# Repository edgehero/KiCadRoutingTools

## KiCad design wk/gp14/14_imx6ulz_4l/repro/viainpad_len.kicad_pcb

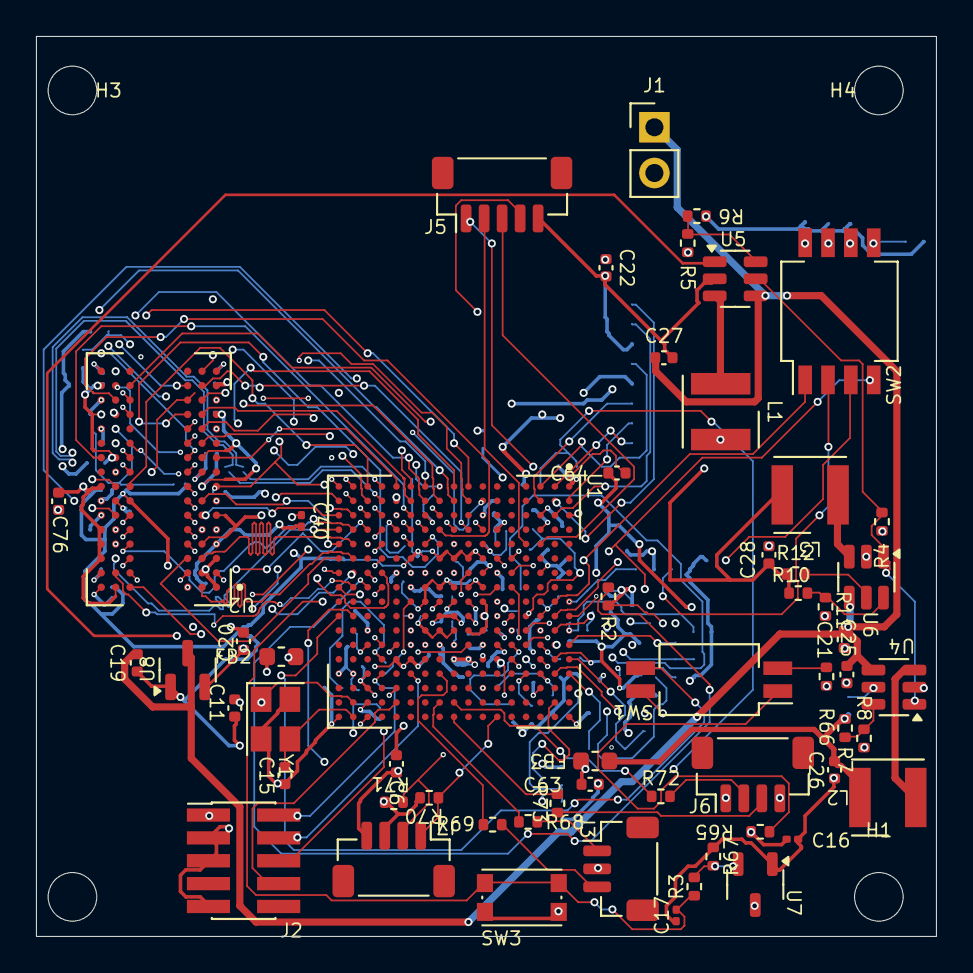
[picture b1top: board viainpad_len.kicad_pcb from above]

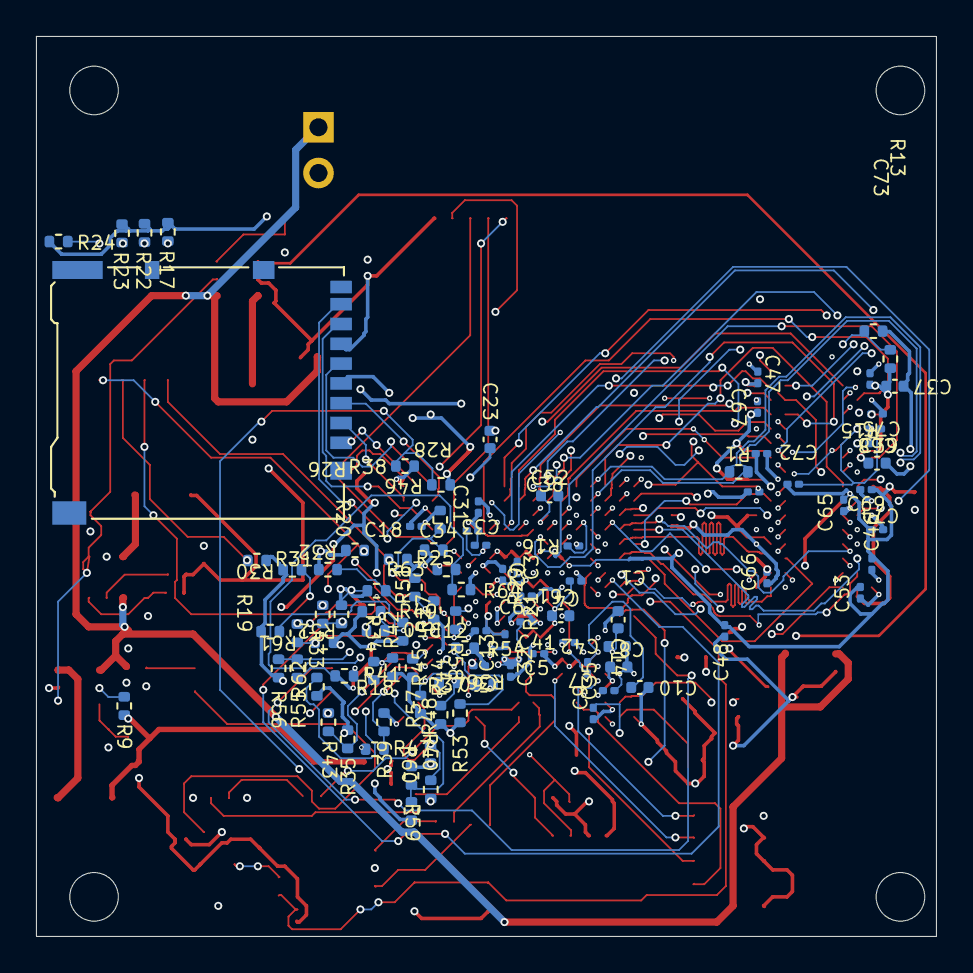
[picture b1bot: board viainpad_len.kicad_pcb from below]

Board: 4 copper layers, 50.0 x 50.0 mm, 159 parts (97 on the bottom side), 134 nets.

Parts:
C1, C2, C3, C5, C7, C9, C12, C13, C16, C17, C18, C31, C32, C33, C34, C35, C36, C38, C39, C40, C41, C46, C47, C48, C53, C60, C61, C62, C65, C66, C67, C69, C72, C73, C74, C75: 0.22u; C_0201_0603Metric
C4, C8, C23, C26, C28, C63, C68, C76: 22uF/20%/X5R/6.3V; C_0402_1005Metric
C6, C21, C25, C27, C37, C64: 4.7u; C_0402_1005Metric
C10, C42, C52: 10u; C_0402_1005Metric
C11, C15: 18p; C_0402_1005Metric
C14: 0.1u; C_0402_1005Metric
C19, C20: 1u; C_0402_1005Metric
C22: 10uF; C_0402_1005Metric
FB2, FB3: 120ohm@100MHz (2A); L_0603_1608Metric
H1, H2, H3, H4: MountingHole; MountingHole_2.7mm_M2.5
J1: Conn_01x02_Pin; PinHeader_1x02_P2.54mm_Vertical
J2: Conn_ARM_JTAG_SWD_10; PinHeader_2x05_P1.27mm_Vertical_SMD
J3: JST_BM03B-SRSS-TB; JST_SH_BM03B-SRSS-TB_1x03-1MP_P1.00mm_Vertical
J4: Micro_SD_Card_Det_Hirose_DM3AT; microSD_HC_Hirose_DM3AT-SF-PEJM5
J5: JST_BM05B-SRSS-TB; JST_SH_BM05B-SRSS-TB_1x05-1MP_P1.00mm_Vertical
J6, J7: JST_BM04B-SRSS-TB; JST_SH_BM04B-SRSS-TB_1x04-1MP_P1.00mm_Vertical
L1, L2, L3: 2.2uH; L_Wurth_WE-LQSH-4020
R1: 470R; R_0402_1005Metric
R2, R4, R9, R12, R25, R26, R27, R28, R29, R30, R31, R32, R33, R34, R35, R36, R37, R38, R39, R40, R41, R42, R43, R44, R45, R46, R47, R48, R49, R50, R51, R52, R53, R54, R55, R56, R57, R58, R59, R60, R61, R62, R63, R64, R65, R66: 10k; R_0402_1005Metric
R3, R17, R18, R19, R20, R21, R22, R23, R24: 1k; R_0402_1005Metric
R5, R8, R11, R67: 100k; R_0402_1005Metric
R6: 549k; R_0402_1005Metric
R7: 113k; R_0402_1005Metric
R10: 124k; R_0402_1005Metric
R13, R14, R71: 1.5k; R_0402_1005Metric
R15, R16: 240R; R_0201_0603Metric
R68, R69, R72, R73: 22R/R0402; R_0402_1005Metric
R70: 1.5K; R_0402_1005Metric
SW1: SW_DIP_x02; SW_DIP_SPSTx02_Slide_Copal_CHS-02B_W7.62mm_P1.27mm
SW2: SW_DIP_x04; SW_DIP_SPSTx04_Slide_Copal_CHS-04B_W7.62mm_P1.27mm
SW3: SW_Push; SW_Push_1P1T_NO_CK_KMR2
U1: MCIMX6Z0DVM09AB; BGA289C80P17X17_1400X1400X132
U2: K4B4G1646E-BCNB; BGA96C80P6X16_800X1400X120
U4, U5, U6: TLV62568DDC; SOT-23-6
U7: LM809; SOT-23-3
U8: MCP1700x-330xxTT; SOT-23
Y1: Crystal_GND24; Crystal_SMD_SeikoEpson_TSX3225-4Pin_3.2x2.5mm

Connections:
+1V2: C26.1, FB3.1, L2.2, R7.1, R9.1
+3V3: C16.1, C18.1, C22.1, C31.1, C32.1, C33.1, C34.1, C35.1, C60.1, FB2.1, J2.1 (VTref), J4.4 (VDD), J6.1, J7.3, L1.2, R2.2, R4.1, R6.1, R17.2, R18.2, R19.2, R20.2, R21.2, R22.2, R23.2, R24.2, R41.2, R42.2, R43.2, R44.2, R45.2, R46.2, R47.2, R48.2, R49.2, R51.2, R53.2, R55.2, R57.2, R59.2, R61.2, R63.2, R65.2, R66.2, R70.2, R71.2, U1.C4 (NVCC_SD1), U1.E7 (NVCC_NAND), U1.E13 (NVCC_GPIO3), U1.F4 (NVCC_SD2), U1.F13 (NVCC_KPP), U1.H13 (NVCC_UART), U1.J13 (NVCC_GPIO), U7.3 (VCC)
+5V: C19.1, C21.1, C25.1, C27.1, J1.1, U4.4 (VIN), U5.4 (VIN), U6.4 (VIN), U8.3 (VI)
/Boot Config, Clock, Reset/BOOT_CFG1_0: R25.2, SW2.1, U1.B9 (GPIO3_IO05)
/Boot Config, Clock, Reset/BOOT_CFG1_0_SW: R17.1, SW2.8
/Boot Config, Clock, Reset/BOOT_CFG1_1: R18.1, R26.2, U1.A9 (GPIO3_IO06)
/Boot Config, Clock, Reset/BOOT_CFG1_2: R19.1, R27.2, U1.E10 (GPIO3_IO07)
/Boot Config, Clock, Reset/BOOT_CFG1_3: R20.1, R28.2, U1.D10 (GPIO3_IO08)
/Boot Config, Clock, Reset/BOOT_CFG1_4: R21.1, R29.2, U1.C10 (GPIO3_IO09)
/Boot Config, Clock, Reset/BOOT_CFG1_5: R30.2, SW2.2, U1.B10 (GPIO3_IO10)
/Boot Config, Clock, Reset/BOOT_CFG1_5_SW: R22.1, SW2.7
/Boot Config, Clock, Reset/BOOT_CFG1_6: R31.2, SW2.3, U1.A10 (GPIO3_IO11)
/Boot Config, Clock, Reset/BOOT_CFG1_6_SW: R23.1, SW2.6
/Boot Config, Clock, Reset/BOOT_CFG1_7: R32.2, SW2.4, U1.D11 (GPIO3_IO12)
/Boot Config, Clock, Reset/BOOT_CFG1_7_SW: R24.1, SW2.5
/Boot Config, Clock, Reset/BOOT_CFG2_0: R49.1, R50.2, U1.B11 (GPIO3_IO13)
/Boot Config, Clock, Reset/BOOT_CFG2_1: R51.1, R52.2, U1.A11 (GPIO3_IO14)
/Boot Config, Clock, Reset/BOOT_CFG2_2: R53.1, R54.2, U1.E12 (GPIO3_IO15)
/Boot Config, Clock, Reset/BOOT_CFG2_3: R55.1, R56.2, U1.D12 (GPIO3_IO16)
/Boot Config, Clock, Reset/BOOT_CFG2_4: R57.1, R58.2, U1.C12 (GPIO3_IO17)
/Boot Config, Clock, Reset/BOOT_CFG2_5: R59.1, R60.2, U1.B12 (GPIO3_IO18)
/Boot Config, Clock, Reset/BOOT_CFG2_6: R61.1, R62.2, U1.A12 (GPIO3_IO19)
/Boot Config, Clock, Reset/BOOT_CFG2_7: R63.1, R64.2, U1.D13 (GPIO3_IO20)
/Boot Config, Clock, Reset/BOOT_CFG4_0: R33.2, R41.1, U1.C13 (GPIO3_IO21)
/Boot Config, Clock, Reset/BOOT_CFG4_1: R34.2, R42.1, U1.B13 (GPIO3_IO22)
/Boot Config, Clock, Reset/BOOT_CFG4_2: R35.2, R43.1, U1.A13 (GPIO3_IO23)
/Boot Config, Clock, Reset/BOOT_CFG4_3: R36.2, R44.1, U1.D14 (GPIO3_IO24)
/Boot Config, Clock, Reset/BOOT_CFG4_4: R37.2, R45.1, U1.C14 (GPIO3_IO25)
/Boot Config, Clock, Reset/BOOT_CFG4_5: R38.2, R46.1, U1.B14 (GPIO3_IO26)
/Boot Config, Clock, Reset/BOOT_CFG4_6: R39.2, R47.1, U1.A14 (GPIO3_IO27)
/Boot Config, Clock, Reset/BOOT_CFG4_7: R40.2, R48.1, U1.B16 (GPIO3_IO28)
/Boot Config, Clock, Reset/BOOT_MODE0: SW1.4, U1.T10 (BOOT_MODE0)
/Boot Config, Clock, Reset/BOOT_MODE1: SW1.3, U1.U10 (BOOT_MODE1)
/Boot Config, Clock, Reset/BOOT_MODE_PU_0: R65.1, SW1.1
/Boot Config, Clock, Reset/BOOT_MODE_PU_1: R66.1, SW1.2
/Boot Config, Clock, Reset/I2C2_SCL: J7.1, R70.1, U1.F17 (I2C2_SCL)
/Boot Config, Clock, Reset/I2C2_SDA: J7.2, R71.1, U1.G13 (I2C2_SDA)
/Boot Config, Clock, Reset/IMX_XI: C11.1, U1.T16 (XTALI), Y1.1
/Boot Config, Clock, Reset/IMX_XO: C15.1, U1.T17 (XTALO), Y1.3
/Boot Config, Clock, Reset/JTAG_TCK: J2.4 (SWDCLK/TCK), U1.M14 (JTAG_TCK)
/Boot Config, Clock, Reset/JTAG_TDI: J2.8 (NC/TDI), U1.N16 (JTAG_TDI)
/Boot Config, Clock, Reset/JTAG_TDO: J2.6 (SWO/TDO), U1.N15 (JTAG_TDO)
/Boot Config, Clock, Reset/JTAG_TMS: J2.2 (SWDIO/TMS), U1.P14 (JTAG_TMS)
/Boot Config, Clock, Reset/NVCC_PLL_OUT: C9.1, C10.1, U1.P13 (NVCC_PLL)
/Boot Config, Clock, Reset/RST_DLY_L: R3.2, R67.1, U7.2 (~RESET)
/Boot Config, Clock, Reset/SOC_ONOFF: R2.1, U1.R8 (ONOFF)
/Boot Config, Clock, Reset/SOC_RST_L: C17.2, R3.1, SW3.1, U1.P8 (POR_B)
/DRAM/DDRCTL_ZQ: R16.1, U1.N4 (DRAM_ZQPAD)
/DRAM/DRAM_AD0: U1.L5 (DRAM_ADDR00), U2.N3 (A0)
/DRAM/DRAM_AD1: U1.H2 (DRAM_ADDR01), U2.P7 (A1)
/DRAM/DRAM_AD2: U1.K1 (DRAM_ADDR02), U2.P3 (A2)
/DRAM/DRAM_AD3: U1.M2 (DRAM_ADDR03), U2.N2 (A3)
/DRAM/DRAM_AD4: U1.K4 (DRAM_ADDR04), U2.P8 (A4)
/DRAM/DRAM_AD5: U1.L1 (DRAM_ADDR05), U2.P2 (A5)
/DRAM/DRAM_AD6: U1.G2 (DRAM_ADDR06), U2.R8 (A6)
/DRAM/DRAM_AD7: U1.H4 (DRAM_ADDR07), U2.R2 (A7)
/DRAM/DRAM_AD8: U1.J4 (DRAM_ADDR08), U2.T8 (A8)
/DRAM/DRAM_AD9: U1.L2 (DRAM_ADDR09), U2.R3 (A9)
/DRAM/DRAM_AD10: U1.M4 (DRAM_ADDR10), U2.L7 (A10/AP)
/DRAM/DRAM_AD11: U1.K3 (DRAM_ADDR11), U2.R7 (A11)
/DRAM/DRAM_AD12: U1.L4 (DRAM_ADDR12), U2.N7 (A12/~BC)
/DRAM/DRAM_BA0: U1.M1 (DRAM_SDBA0), U2.M2 (BA0)
/DRAM/DRAM_BA1: U1.H1 (DRAM_SDBA1), U2.N8 (BA1)
/DRAM/DRAM_BA2: U1.K2 (DRAM_SDBA2), U2.M3 (BA2)
/DRAM/DRAM_CAS_L: U1.J2 (DRAM_CAS_B), U2.K3 (~CAS)
/DRAM/DRAM_CKE: U1.M3 (DRAM_SDCKE0), U2.K9 (CKE)
/DRAM/DRAM_CLK0_N: R1.2, U1.P2 (DRAM_SDCLK0_N), U2.K7 (~CK)
/DRAM/DRAM_CLK0_P: R1.1, U1.P1 (DRAM_SDCLK0_P), U2.J7 (CK)
/DRAM/DRAM_CS0_L: U1.N2 (DRAM_CS0_B), U2.L2 (~CS)
/DRAM/DRAM_DQ0: U1.T4 (DRAM_DATA00), U2.D7 (DQ8)
/DRAM/DRAM_DQ1: U1.U6 (DRAM_DATA01), U2.C3 (DQ9)
/DRAM/DRAM_DQ2: U1.T6 (DRAM_DATA02), U2.A2 (DQ13)
/DRAM/DRAM_DQ3: U1.U7 (DRAM_DATA03), U2.A3 (DQ15)
/DRAM/DRAM_DQ4: U1.U8 (DRAM_DATA04), U2.A7 (DQ12)
/DRAM/DRAM_DQ5: U1.T8 (DRAM_DATA05), U2.B8 (DQ14)
/DRAM/DRAM_DQ6: U1.T5 (DRAM_DATA06), U2.C2 (DQ11)
/DRAM/DRAM_DQ7: U1.U4 (DRAM_DATA07), U2.C8 (DQ10)
/DRAM/DRAM_DQ8: U1.U2 (DRAM_DATA08), U2.E3 (DQ0)
/DRAM/DRAM_DQ9: U1.U3 (DRAM_DATA09), U2.F2 (DQ2)
/DRAM/DRAM_DQ10: U1.U5 (DRAM_DATA10), U2.G2 (DQ6)
/DRAM/DRAM_DQ11: U1.R4 (DRAM_DATA11), U2.F8 (DQ3)
/DRAM/DRAM_DQ12: U1.P5 (DRAM_DATA12), U2.F7 (DQ1)
/DRAM/DRAM_DQ13: U1.P3 (DRAM_DATA13), U2.H3 (DQ4)
/DRAM/DRAM_DQ14: U1.R2 (DRAM_DATA14), U2.H8 (DQ5)
/DRAM/DRAM_DQ15: U1.R1 (DRAM_DATA15), U2.H7 (DQ7)
/DRAM/DRAM_DQM0: U1.T7 (DRAM_DQM0), U2.D3 (UDM)
/DRAM/DRAM_DQM1: U1.T3 (DRAM_DQM1), U2.E7 (LDM)
/DRAM/DRAM_DQS0_N: U1.P7 (DRAM_SDQS0_N), U2.B7 (~UDQS)
/DRAM/DRAM_DQS0_P: U1.P6 (DRAM_SDQS0_P), U2.C7 (UDQS)
/DRAM/DRAM_DQS1_N: U1.T2 (DRAM_SDQS1_N), U2.G3 (~LDQS)
/DRAM/DRAM_DQS1_P: U1.T1 (DRAM_SDQS1_P), U2.F3 (LDQS)
/DRAM/DRAM_ODT: U1.N1 (DRAM_ODT0), U2.K1 (ODT)
/DRAM/DRAM_RAS_L: U1.M5 (DRAM_RAS_B), U2.J3 (~RAS)
/DRAM/DRAM_RST_L: U1.G4 (DRAM_RESET), U2.T2 (~RESET)
/DRAM/DRAM_VREF: C36.2, C38.1, C39.1, C40.1, R13.2, R14.1, U1.P4 (DRAM_VREF), U2.H1 (VREFDQ), U2.M8 (VREFCA)
/DRAM/DRAM_WE_L: U1.J1 (DRAM_SDWE_B), U2.L3 (~WE)
/DRAM/DRAM_ZQ: R15.1, U2.L8 (ZQ)
/IO and Peripherals/FTDI_RXD: J3.1, R68.2
/IO and Peripherals/FTDI_TXD: J3.3, R69.2
/IO and Peripherals/QSPIA_CS_L: J5.4, U1.E6 (NAND_DQS)
/IO and Peripherals/QSPIA_D0: J5.1, U1.A3 (NAND_READY_B)
/IO and Peripherals/QSPIA_D1: J5.3, U1.C5 (NAND_CE0_B)
/IO and Peripherals/QSPIA_SCLK: J5.2, U1.D5 (NAND_WP_B)
/IO and Peripherals/UART1_RX: R68.1, U1.K16 (UART1_RX_DATA)
/IO and Peripherals/UART1_TX: R69.1, U1.K14 (UART1_TX_DATA)
/IO and Peripherals/UART2_RX: R72.1, U1.J16 (UART2_RX_DATA)
/IO and Peripherals/UART2_RX_R: J6.2, R72.2
/IO and Peripherals/UART2_TX: R73.1, U1.J17 (UART2_TX_DATA)
/IO and Peripherals/UART2_TX_R: J6.3, R73.2
/SDcard/SD1_CLK: J4.5 (CLK), U1.C1 (SD1_CLK)
/SDcard/SD1_CMD: J4.3 (CMD), U1.C2 (SD1_CMD)
/SDcard/SD1_D0: J4.7 (DAT0), U1.B3 (SD1_DATA0)
/SDcard/SD1_D1: J4.8 (DAT1), U1.B2 (SD1_DATA1)
/SDcard/SD1_D2: J4.1 (DAT2), U1.B1 (SD1_DATA2)
/SDcard/SD1_D3: J4.2 (DAT3/CD), U1.A2 (SD1_DATA3)
/SOC Power/V1P27_FB: R7.2, R8.1, U4.6 (FB)
/SOC Power/V1P27_PG: R9.2, U4.5 (PG)
/SOC Power/V1P27_SW: L2.1, U4.3 (SW)
/SOC Power/V3P3_FB: R5.1, R6.2, U5.6 (FB)
/SOC Power/V3P3_PG: R4.2, U4.1 (EN), U5.5 (PG), U6.1 (EN)
/SOC Power/V3P3_SW: L1.1, U5.3 (SW)
/SOC Power/VDD_ARM_CAP: C12.1, C13.1, C23.1, U1.G9 (VDD_ARM_CAP), U1.G10 (VDD_ARM_CAP__1), U1.G11 (VDD_ARM_CAP__2), U1.H11 (VDD_ARM_CAP__3)
/SOC Power/VDD_ARM_SOC_IN: C61.1, C62.1, C63.1, C64.1, FB3.2, U1.H9 (VDD_SOC_IN), U1.H10 (VDD_SOC_IN__1), U1.J9 (VDD_SOC_IN__2), U1.J10 (VDD_SOC_IN__3), U1.K9 (VDD_SOC_IN__4), U1.K10 (VDD_SOC_IN__5)
/SOC Power/VDD_HIGH_CAP: C7.1, C8.1, U1.R14 (VDD_HIGH_CAP), U1.R15 (VDD_HIGH_CAP__1)
/SOC Power/VDD_HIGH_IN: C5.1, C6.1, FB2.2, U1.L13 (VDD_HIGH_IN), U1.M13 (VDD_HIGH_IN__1), U1.N13 (VDD_HIGH_IN__2)
/SOC Power/VDD_SNVS_CAP: C41.1, U1.N12 (VDD_SNVS_CAP)
/SOC Power/VDD_SNVS_IN: C20.1, U1.P12 (VDD_SNVS_IN), U5.1 (EN), U8.2 (VO)
/SOC Power/VDD_SOC_CAP: C1.1, C2.1, C3.1, C4.1, U1.G8 (VDD_SOC_CAP), U1.H8 (VDD_SOC_CAP__1), U1.J8 (VDD_SOC_CAP__2), U1.J11 (VDD_SOC_CAP__3), U1.K8 (VDD_SOC_CAP__4), U1.K11 (VDD_SOC_CAP__5), U1.L8 (VDD_SOC_CAP__6), U1.L9 (VDD_SOC_CAP__7), U1.L10 (VDD_SOC_CAP__8), U1.L11 (VDD_SOC_CAP__9)
/SOC Power/VDD_USB_CAP: C14.1, C42.1, U1.R12 (VDD_USB_CAP)
/SOC Power/VMEM_FB: R10.2, R11.1, U6.6 (FB)
/SOC Power/VMEM_PG: R12.2, U6.5 (PG)
/SOC Power/VMEM_SW: L3.1, U6.3 (SW)
GND: C1.2, C2.2, C3.2, C4.2, C5.2, C6.2, C7.2, C8.2, C9.2, C10.2, C11.2, C12.2, C13.2, C14.2, C15.2, C16.2, C17.1, C18.2, C19.2, C20.2, C21.2, C22.2, C23.2, C25.2, C26.2, C27.2, C28.2, C31.2, C32.2, C33.2, C34.2, C35.2, C37.2, C38.2, C39.2, C40.2, C41.2, C42.2, C46.2, C47.2, C48.2, C52.2, C53.2, C60.2, C61.2, C62.2, C63.2, C64.2, C65.2, C66.2, C67.2, C68.2, C69.2, C72.2, C73.2, C74.2, C75.2, C76.2, J1.2, J2.3 (GND), J2.5 (GND), J2.9 (GNDDetect), J3.2, J4.6 (VSS), J5.5, J6.4, J7.4, R5.2, R8.2, R11.2, R14.2, R15.2, R16.2, R25.1, R26.1, R27.1, R28.1, R29.1, R30.1, R31.1, R32.1, R33.1, R34.1, R35.1, R36.1, R37.1, R38.1, R39.1, R40.1, R50.1, R52.1, R54.1, R56.1, R58.1, R60.1, R62.1, R64.1, R67.2, SW3.2, U1.A1 (VSS), U1.A17 (VSS__1), U1.C3 (VSS__2), U1.C7 (VSS__3), U1.C11 (VSS__4), U1.C15 (VSS__5), U1.E8 (VSS__6), U1.E11 (VSS__7), U1.F6 (VSS__8), U1.F7 (VSS__9), U1.F8 (VSS_1), U1.F9 (VSS_1__1), U1.F10 (VSS_1__2), U1.F11 (VSS_1__3), U1.F12 (VSS_1__4), U1.G3 (VSS_1__5), U1.G5 (VSS_1__6), U1.G7 (VSS_1__7), U1.G12 (VSS_1__8), U1.G15 (VSS_1__9), U1.H7 (VSS_2), U1.H12 (VSS_2__1), U1.J5 (VSS_2__2), U1.J7 (VSS_2__3), U1.J12 (VSS_2__4), U1.K7 (VSS_2__5), U1.K12 (VSS_2__6), U1.L3 (VSS_2__7), U1.L7 (VSS_2__8), U1.L12 (VSS_2__9), U1.M7 (VSS_3), U1.M8 (VSS_3__1), U1.M9 (VSS_3__2), U1.M10 (VSS_3__3), U1.M11 (VSS_3__4), U1.M12 (NGND_KEL0), U1.N3 (VSS_3__5), U1.N5 (VSS_3__6), U1.N7 (TEST_MODE), U1.R3 (VSS_3__7), U1.R5 (VSS_3__8), U1.R7 (VSS_3__9), U1.R11 (VSS_4), U1.R16 (VSS_4__1), U1.R17 (VSS_4__2), U1.T14 (VSS_4__3), U1.U1 (VSS_4__4), U1.U14 (VSS_4__5), U1.U17 (VSS_4__6), U2.A9 (VSS), U2.B1 (VSSQ), U2.B3 (VSS__1), U2.B9 (VSSQ__1), U2.D1 (VSSQ__2), U2.D8 (VSSQ__3), U2.E1 (VSS__2), U2.E2 (VSSQ__4), U2.E8 (VSSQ__5), U2.F9 (VSSQ__6), U2.G1 (VSSQ__7), U2.G8 (VSS__3), U2.G9 (VSSQ__8), U2.J2 (VSS__4), U2.J8 (VSS__5), U2.M1 (VSS__6), U2.M9 (VSS__7), U2.P1 (VSS__8), U2.P9 (VSS__9), U2.T1 (VSS__10), U2.T9 (VSS__11), U4.2 (GND), U5.2 (GND), U6.2 (GND), U7.1 (GND), U8.1 (GND), Y1.2, Y1.4
VMEM: C28.1, C36.1, C37.1, C46.1, C47.1, C48.1, C52.1, C53.1, C65.1, C66.1, C67.1, C68.1, C69.1, C72.1, C73.1, C74.1, C75.1, C76.1, L3.2, R10.1, R12.1, R13.1, U1.G6 (NVCC_DRAM), U1.H6 (NVCC_DRAM__1), U1.J6 (NVCC_DRAM__2), U1.K6 (NVCC_DRAM__3), U1.L6 (NVCC_DRAM__4), U1.M6 (NVCC_DRAM__5), U2.A1 (VDDQ), U2.A8 (VDDQ__1), U2.B2 (VDD), U2.C1 (VDDQ__2), U2.C9 (VDDQ__3), U2.D2 (VDDQ__4), U2.D9 (VDD__1), U2.E9 (VDDQ__5), U2.F1 (VDDQ__6), U2.G7 (VDD__2), U2.H2 (VDDQ__7), U2.H9 (VDDQ__8), U2.K2 (VDD__3), U2.K8 (VDD__4), U2.N1 (VDD__5), U2.N9 (VDD__6), U2.R1 (VDD__7), U2.R9 (VDD__8)

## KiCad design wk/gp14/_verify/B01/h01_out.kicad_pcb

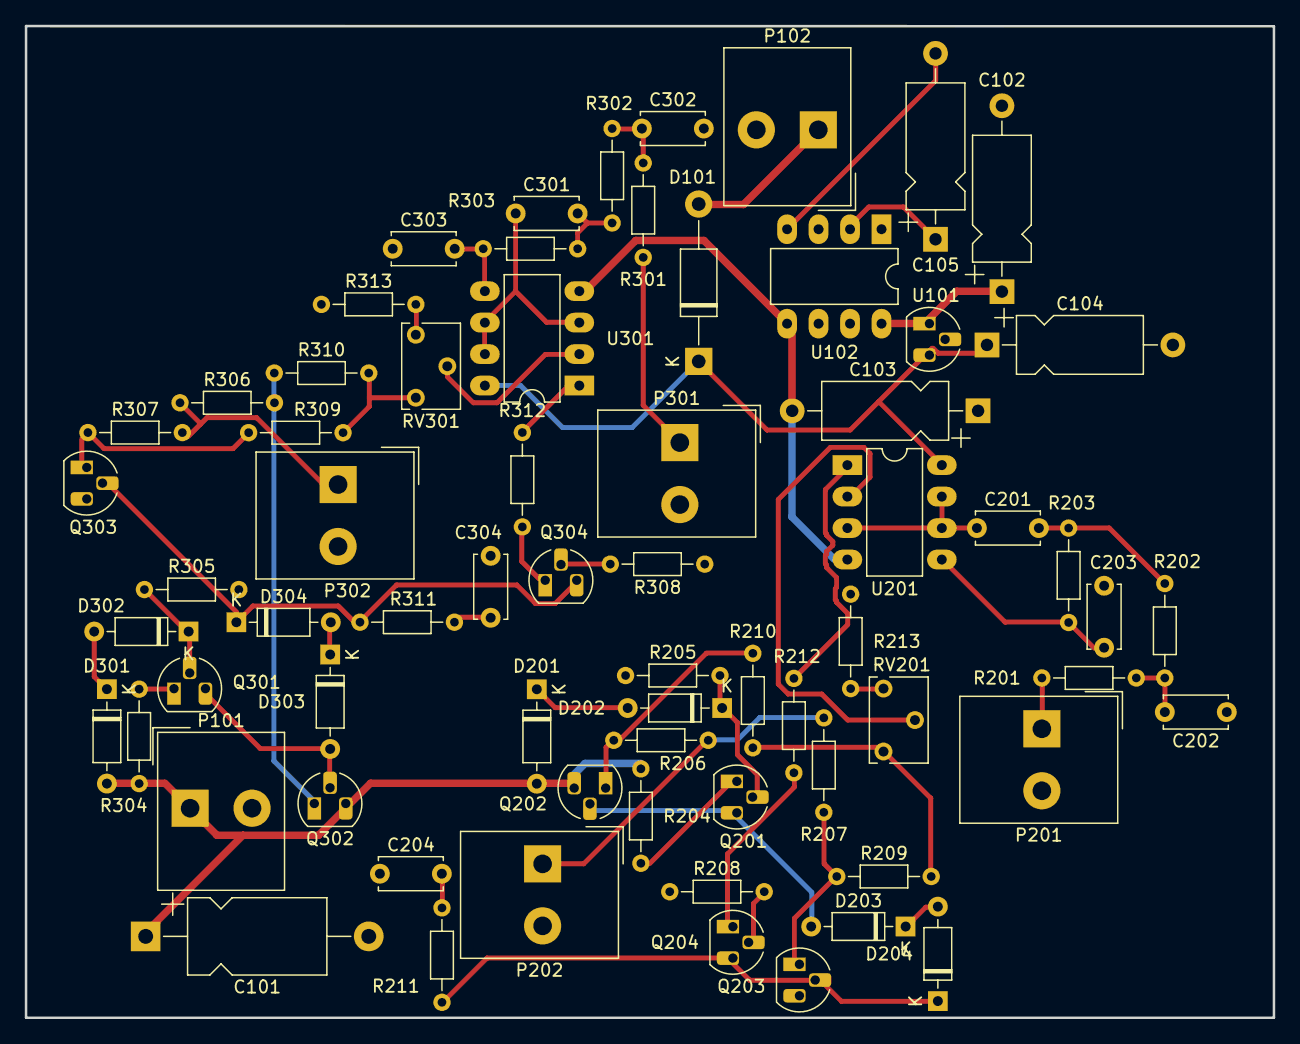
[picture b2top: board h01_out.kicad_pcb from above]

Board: 2 copper layers, 100.7 x 80.0 mm, 68 parts (0 on the bottom side), 50 nets.

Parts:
C101: 47uF/63V; CP_Axial_L11.0mm_D6.0mm_P18.00mm_Horizontal
C102: 47uF; CP_Axial_L10.0mm_D4.5mm_P15.00mm_Horizontal
C103, C105: 10uF; CP_Axial_L10.0mm_D4.5mm_P15.00mm_Horizontal
C104: 47uF/20V; CP_Axial_L10.0mm_D4.5mm_P15.00mm_Horizontal
C201, C301: 15nF; C_Disc_D5.0mm_W2.5mm_P5.00mm
C202, C302: 150nF; C_Disc_D5.0mm_W2.5mm_P5.00mm
C203, C303: 4.7nF; C_Disc_D5.0mm_W2.5mm_P5.00mm
C204, C304: 820pF; C_Disc_D5.0mm_W2.5mm_P5.00mm
D101: 1N4007; D_DO-41_SOD81_P12.70mm_Horizontal
D201, D202, D203, D204, D301, D302, D303, D304: 1N4148; D_DO-35_SOD27_P7.62mm_Horizontal
P101, P102, P201, P202, P301, P302: CONN_2; Altech_AK300_1x02_P5.00mm_45-Degree
Q201, Q203, Q301, Q303: MPSA92; TO-92_HandSolder
Q202, Q204, Q302, Q304: MPSA42; TO-92_HandSolder
R201, R208, R212, R301, R308, R312: 1K; R_Axial_DIN0204_L3.6mm_D1.6mm_P7.62mm_Horizontal
R202, R203, R302, R303: 22K; R_Axial_DIN0204_L3.6mm_D1.6mm_P7.62mm_Horizontal
R204, R304: 470; R_Axial_DIN0204_L3.6mm_D1.6mm_P7.62mm_Horizontal
R205, R209, R210, R305, R309, R310: 220K; R_Axial_DIN0204_L3.6mm_D1.6mm_P7.62mm_Horizontal
R206, R207, R306, R307: 47; R_Axial_DIN0204_L3.6mm_D1.6mm_P7.62mm_Horizontal
R211, R311: 5,6K; R_Axial_DIN0204_L3.6mm_D1.6mm_P7.62mm_Horizontal
R213, R313: 4,7K; R_Axial_DIN0204_L3.6mm_D1.6mm_P7.62mm_Horizontal
RV201, RV301: 4,7K; Potentiometer_Bourns_3266W_Vertical
U101: 78L05; TO-92_HandSolder
U102: ICL7660; DIP-8_W7.62mm_LongPads
U201, U301: LM358N; DIP-8_W7.62mm_LongPads

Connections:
+12V: C104.1, D101.1 (K), U101.3 (VI), U201.8 (V+), U301.8 (V+)
-VAA: C103.2, U102.5 (VOUT), U201.4 (V-), U301.4 (V-)
/12Vext: D101.2 (A), P102.1
/ampli_ht_horizontal/PIEZO_IN: P301.1, R301.2
/ampli_ht_horizontal/PIEZO_OUT: P302.1, R306.1, R307.1
/ampli_ht_horizontal/S_OUT+: R309.1, R310.1, RV301.3
/ampli_ht_horizontal/Vpil_0_3,3V: C301.1, U301.3 (+), U301.6 (-), U301.7
/ampli_ht_vertical/PIEZO_IN: P201.1, R201.2
/ampli_ht_vertical/PIEZO_OUT: P202.1, R206.1, R207.1
/ampli_ht_vertical/S_OUT+: R209.1, R210.1, RV201.3
/ampli_ht_vertical/Vpil_0_3,3V: C201.1, U201.3 (+), U201.6 (-), U201.7
GND: C101.2, C102.2, C103.1, C104.2, C202.2, C203.2, C204.2, C302.2, C303.2, C304.2, P101.2 (PM), P102.2 (PM), P201.2 (PM), P202.2 (PM), P301.2 (PM), P302.2 (PM), Q203.3 (C), Q303.3 (C), R205.2, R208.2, R213.2, R305.2, R308.2, R313.2, U101.2 (GND), U102.3 (GND)
HT: C101.1, D201.2 (A), D301.2 (A), P101.1, Q202.3 (C), Q302.3 (C), R204.1, R304.1
unnamed: C201.2, R202.1, R203.2
unnamed: C202.1, R201.1, R202.2
unnamed: C204.1, R211.2
unnamed: C301.2, R302.1, R303.2
unnamed: C302.1, R301.1, R302.2
unnamed: C304.1, R311.2
unnamed: D201.1 (K), D202.2 (A)
unnamed: D202.1 (K), Q201.2 (B), R205.1
unnamed: D203.2 (A), Q201.3 (C), Q202.2 (B)
unnamed: D203.1 (K), D204.2 (A)
unnamed: D204.1 (K), Q203.2 (B), Q204.3 (C), R211.1
unnamed: D301.1 (K), D302.2 (A)
unnamed: D302.1 (K), Q301.2 (B), R305.1
unnamed: D303.2 (A), Q301.3 (C), Q302.2 (B)
unnamed: D303.1 (K), D304.2 (A)
unnamed: D304.1 (K), Q303.2 (B), Q304.3 (C), R311.1
unnamed: Q201.1 (E), R204.2
unnamed: Q202.1 (E), R206.2, R210.2
unnamed: Q203.1 (E), R207.2, R209.2
unnamed: Q204.2 (B), R208.1
unnamed: Q204.1 (E), R212.1
unnamed: Q301.1 (E), R304.2
unnamed: Q302.1 (E), R306.2, R310.2
unnamed: Q303.1 (E), R307.2, R309.2
unnamed: Q304.2 (B), R308.1
unnamed: Q304.1 (E), R312.1
unnamed: R212.2, U201.1
unnamed: R213.1, RV201.1
unnamed: R312.2, U301.1
unnamed: R313.1, RV301.1
unnamed: C105.1, U102.2 (CAP+)
unnamed: C105.2, U102.4 (CAP-)
unnamed: RV201.2, U201.2 (-)
unnamed: C203.1, R203.1, U201.5 (+)
unnamed: RV301.2, U301.2 (-)
unnamed: C303.1, R303.1, U301.5 (+)
VCC: C102.1, U101.1 (VO), U102.8 (V+)

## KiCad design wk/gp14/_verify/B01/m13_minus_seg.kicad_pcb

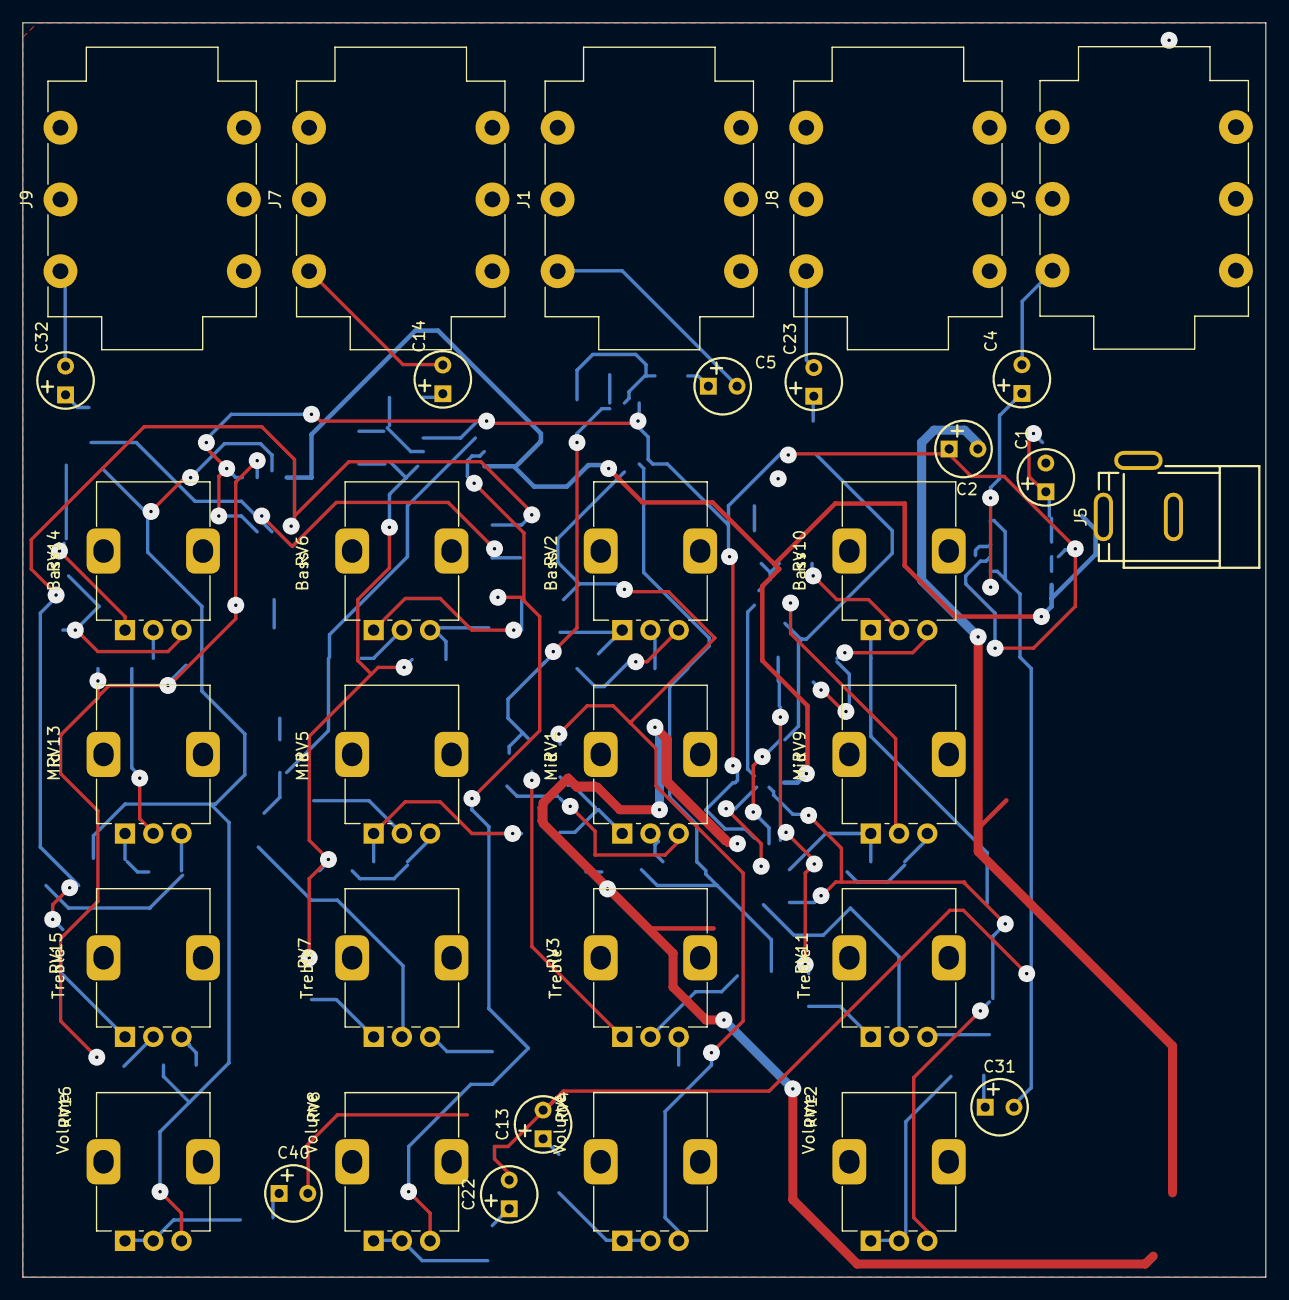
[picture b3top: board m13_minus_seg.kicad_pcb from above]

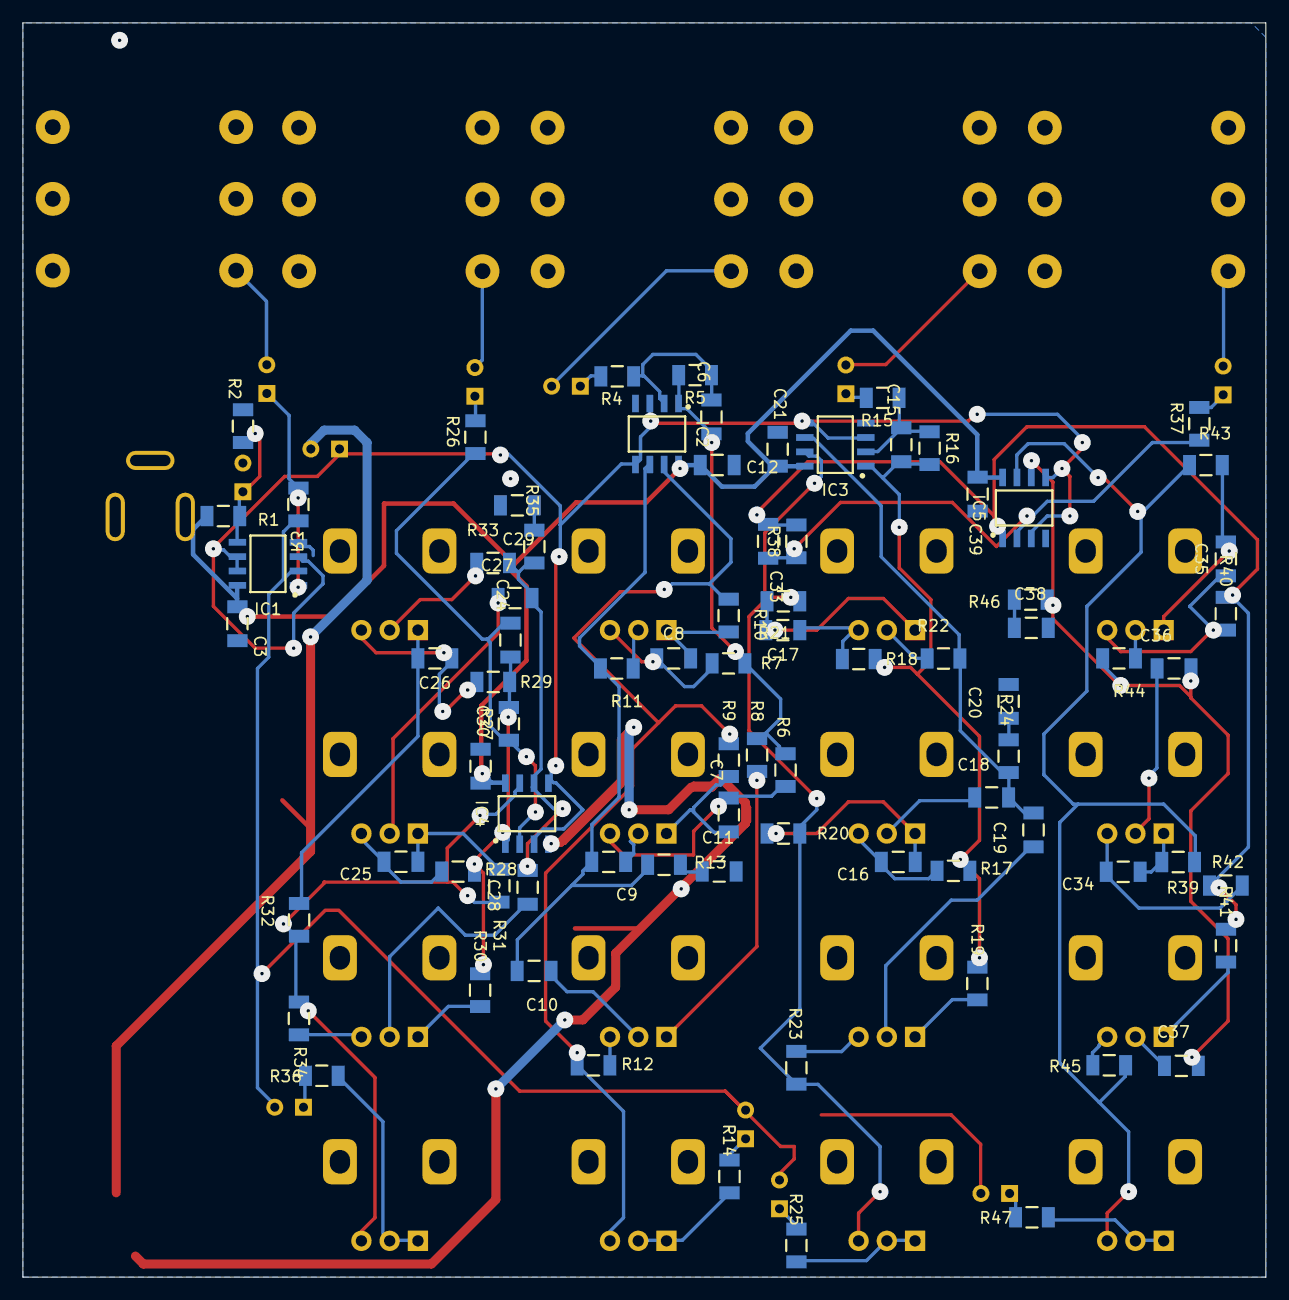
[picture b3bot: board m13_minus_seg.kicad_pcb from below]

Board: 2 copper layers, 110.0 x 111.0 mm, 114 parts (81 on the bottom side), 79 nets.

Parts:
C1, C2, C4, C5, C13, C14, C22, C23, C31, C32, C40: CTEB_2.2UF_35V_10%_254-500X840; CAPPRB254-500X840
C3, C6, C7, C8, C9, C10, C11, C12, C15, C16, C17, C18, C19, C20, C21, C24, C25, C26, C27, C28, C29, C30, C33, C34, C35, C36, C37, C38, C39: CC1206_100NF_50V_10%_X7R; CAPC3216X140N
IC1, IC2, IC3, IC4, IC5: TL072CD; SOIC127P600X175-8N
J1, J6, J7, J8, J9: CH1; Jack_6.35mm_Neutrik_NMJ6HCD2_Horizontal
J5: Power; CLIFF_FC68148(DC-10A)
R1, R2, R3, R4, R5, R6, R7, R8, R9, R10, R11, R12, R13, R14, R15, R16, R17, R18, R19, R20, R21, R22, R23, R24, R25, R26, R27, R28, R29, R30, R31, R32, R33, R34, R35, R36, R37, R38, R39, R40, R41, R42, R43, R44, R45, R46, R47: R1206_10K_1%_0.25W_100PPM; RESC3216X65N
RV1, RV5, RV9, RV13: Mid; Potentiometer_Alps_RK09K_Single_Vertical
RV2, RV6, RV10, RV14: Bass; Potentiometer_Alps_RK09K_Single_Vertical
RV3, RV7, RV11, RV15: Treble; Potentiometer_Alps_RK09K_Single_Vertical
RV4, RV8, RV12, RV16: Volume; Potentiometer_Alps_RK09K_Single_Vertical

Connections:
+12V: C3.2, C12.2, C21.2, C30.2, C39.2, IC1.8 (V+), IC2.8 (V+), IC3.8 (V+), IC4.8 (V+), IC5.8 (V+), J5.1, R1.2
/CH1/OUT: C13.2, C22.2, C31.2, C40.2, IC1.2 (IN-), R3.1
GND: C1.2, C2.2, C3.1, C11.1, C12.1, C20.1, C21.1, C29.1, C30.1, C38.1, C39.1, IC1.4 (V-), IC2.4 (V-), IC3.4 (V-), IC4.4 (V-), IC5.4 (V-), J1.R, J1.S, J5.2, J5.3, J6.S, J7.R, J7.S, J8.R, J8.S, J9.R, J9.S, R2.1
unnamed: C4.2, J6.T
unnamed: C5.1, R4.1
unnamed: C5.2, J1.T
unnamed: C7.1, R6.2, RV1.3
unnamed: C7.2, R9.1, RV1.1
unnamed: C8.1, R7.2, RV2.3
unnamed: C8.2, R10.1, RV2.1
unnamed: C9.1, RV1.2
unnamed: C10.1, RV3.2
unnamed: C11.2, R13.1
unnamed: C13.1, R14.2
unnamed: C14.1, R15.1
unnamed: C14.2, J7.T
unnamed: C16.1, R17.2, RV5.3
unnamed: C16.2, R20.1, RV5.1
unnamed: C17.1, R18.2, RV6.3
unnamed: C17.2, R21.1, RV6.1
unnamed: C18.1, RV5.2
unnamed: C19.1, RV7.2
unnamed: C20.2, R24.1
unnamed: C22.1, R25.2
unnamed: C23.1, R26.1
unnamed: C23.2, J8.T
unnamed: C25.1, R28.2, RV9.3
unnamed: C25.2, R31.1, RV9.1
unnamed: C26.1, R29.2, RV10.3
unnamed: C26.2, R32.1, RV10.1
unnamed: C27.1, RV9.2
unnamed: C28.1, RV11.2
unnamed: C29.2, R35.1
unnamed: C31.1, R36.2
unnamed: C32.1, R37.1
unnamed: C32.2, J9.T
unnamed: C34.1, R39.2, RV13.3
unnamed: C34.2, R42.1, RV13.1
unnamed: C35.1, R40.2, RV14.3
unnamed: C35.2, R43.1, RV14.1
unnamed: C36.1, RV13.2
unnamed: C37.1, RV15.2
unnamed: C38.2, R46.1
unnamed: C40.1, R47.2
unnamed: C4.1, IC1.1 (OUT), R3.2
unnamed: C1.1, IC1.5 (IN+), R1.1, R2.2
unnamed: C6.1, IC2.2 (IN-), R4.2, R5.1
unnamed: C6.2, IC2.1 (OUT), R5.2, R6.1, R7.1, R8.2
unnamed: C9.2, C10.2, IC2.6 (IN-), R11.2, R13.2
unnamed: IC2.7 (OUT), R9.2, R10.2, R12.1, RV4.3
unnamed: C15.1, IC3.2 (IN-), R15.2, R16.1
unnamed: C15.2, IC3.1 (OUT), R16.2, R17.1, R18.1, R19.2
unnamed: C18.2, C19.2, IC3.6 (IN-), R22.2, R24.2
unnamed: IC3.7 (OUT), R20.2, R21.2, R23.1, RV8.3
unnamed: C24.1, IC4.2 (IN-), R26.2, R27.1
unnamed: C24.2, IC4.1 (OUT), R27.2, R28.1, R29.1, R30.2
unnamed: C27.2, C28.2, IC4.6 (IN-), R33.2, R35.2
unnamed: IC4.7 (OUT), R31.2, R32.2, R34.1, RV12.3
unnamed: C33.1, IC5.2 (IN-), R37.2, R38.1
unnamed: C33.2, IC5.1 (OUT), R38.2, R39.1, R40.1, R41.2
unnamed: C36.2, C37.2, IC5.6 (IN-), R44.2, R46.2
unnamed: IC5.7 (OUT), R42.2, R43.2, R45.1, RV16.3
unnamed: R8.1, RV3.1
unnamed: R11.1, RV2.2
unnamed: R12.2, RV3.3
unnamed: R14.1, RV4.1, RV4.2
unnamed: R19.1, RV7.1
unnamed: R22.1, RV6.2
unnamed: R23.2, RV7.3
unnamed: R25.1, RV8.1, RV8.2
unnamed: R30.1, RV11.1
unnamed: R33.1, RV10.2
unnamed: R34.2, RV11.3
unnamed: R36.1, RV12.1, RV12.2
unnamed: R41.1, RV15.1
unnamed: R44.1, RV14.2
unnamed: R45.2, RV15.3
unnamed: R47.1, RV16.1, RV16.2
vbias: C2.1, IC1.3 (IN+), IC1.6 (IN-), IC1.7 (OUT), IC2.3 (IN+), IC2.5 (IN+), IC3.3 (IN+), IC3.5 (IN+), IC4.3 (IN+), IC4.5 (IN+), IC5.3 (IN+), IC5.5 (IN+)

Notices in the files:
parts and their libraries:
License: This work is licensed under the Creative Commons CC-BY-SA 4.0 License. To the extent that circuit schematics that use Licensed Material can be considered to be ‘Adapted Material’, then the copyright holder waives article 3.b of the license with respect to these schematics.
